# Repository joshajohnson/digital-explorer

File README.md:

Digital explorer board for common embedded protocols (UART, I2C, SPI, WS2812).

More info here: https://joshajohnson.com/digital-explorer-board/

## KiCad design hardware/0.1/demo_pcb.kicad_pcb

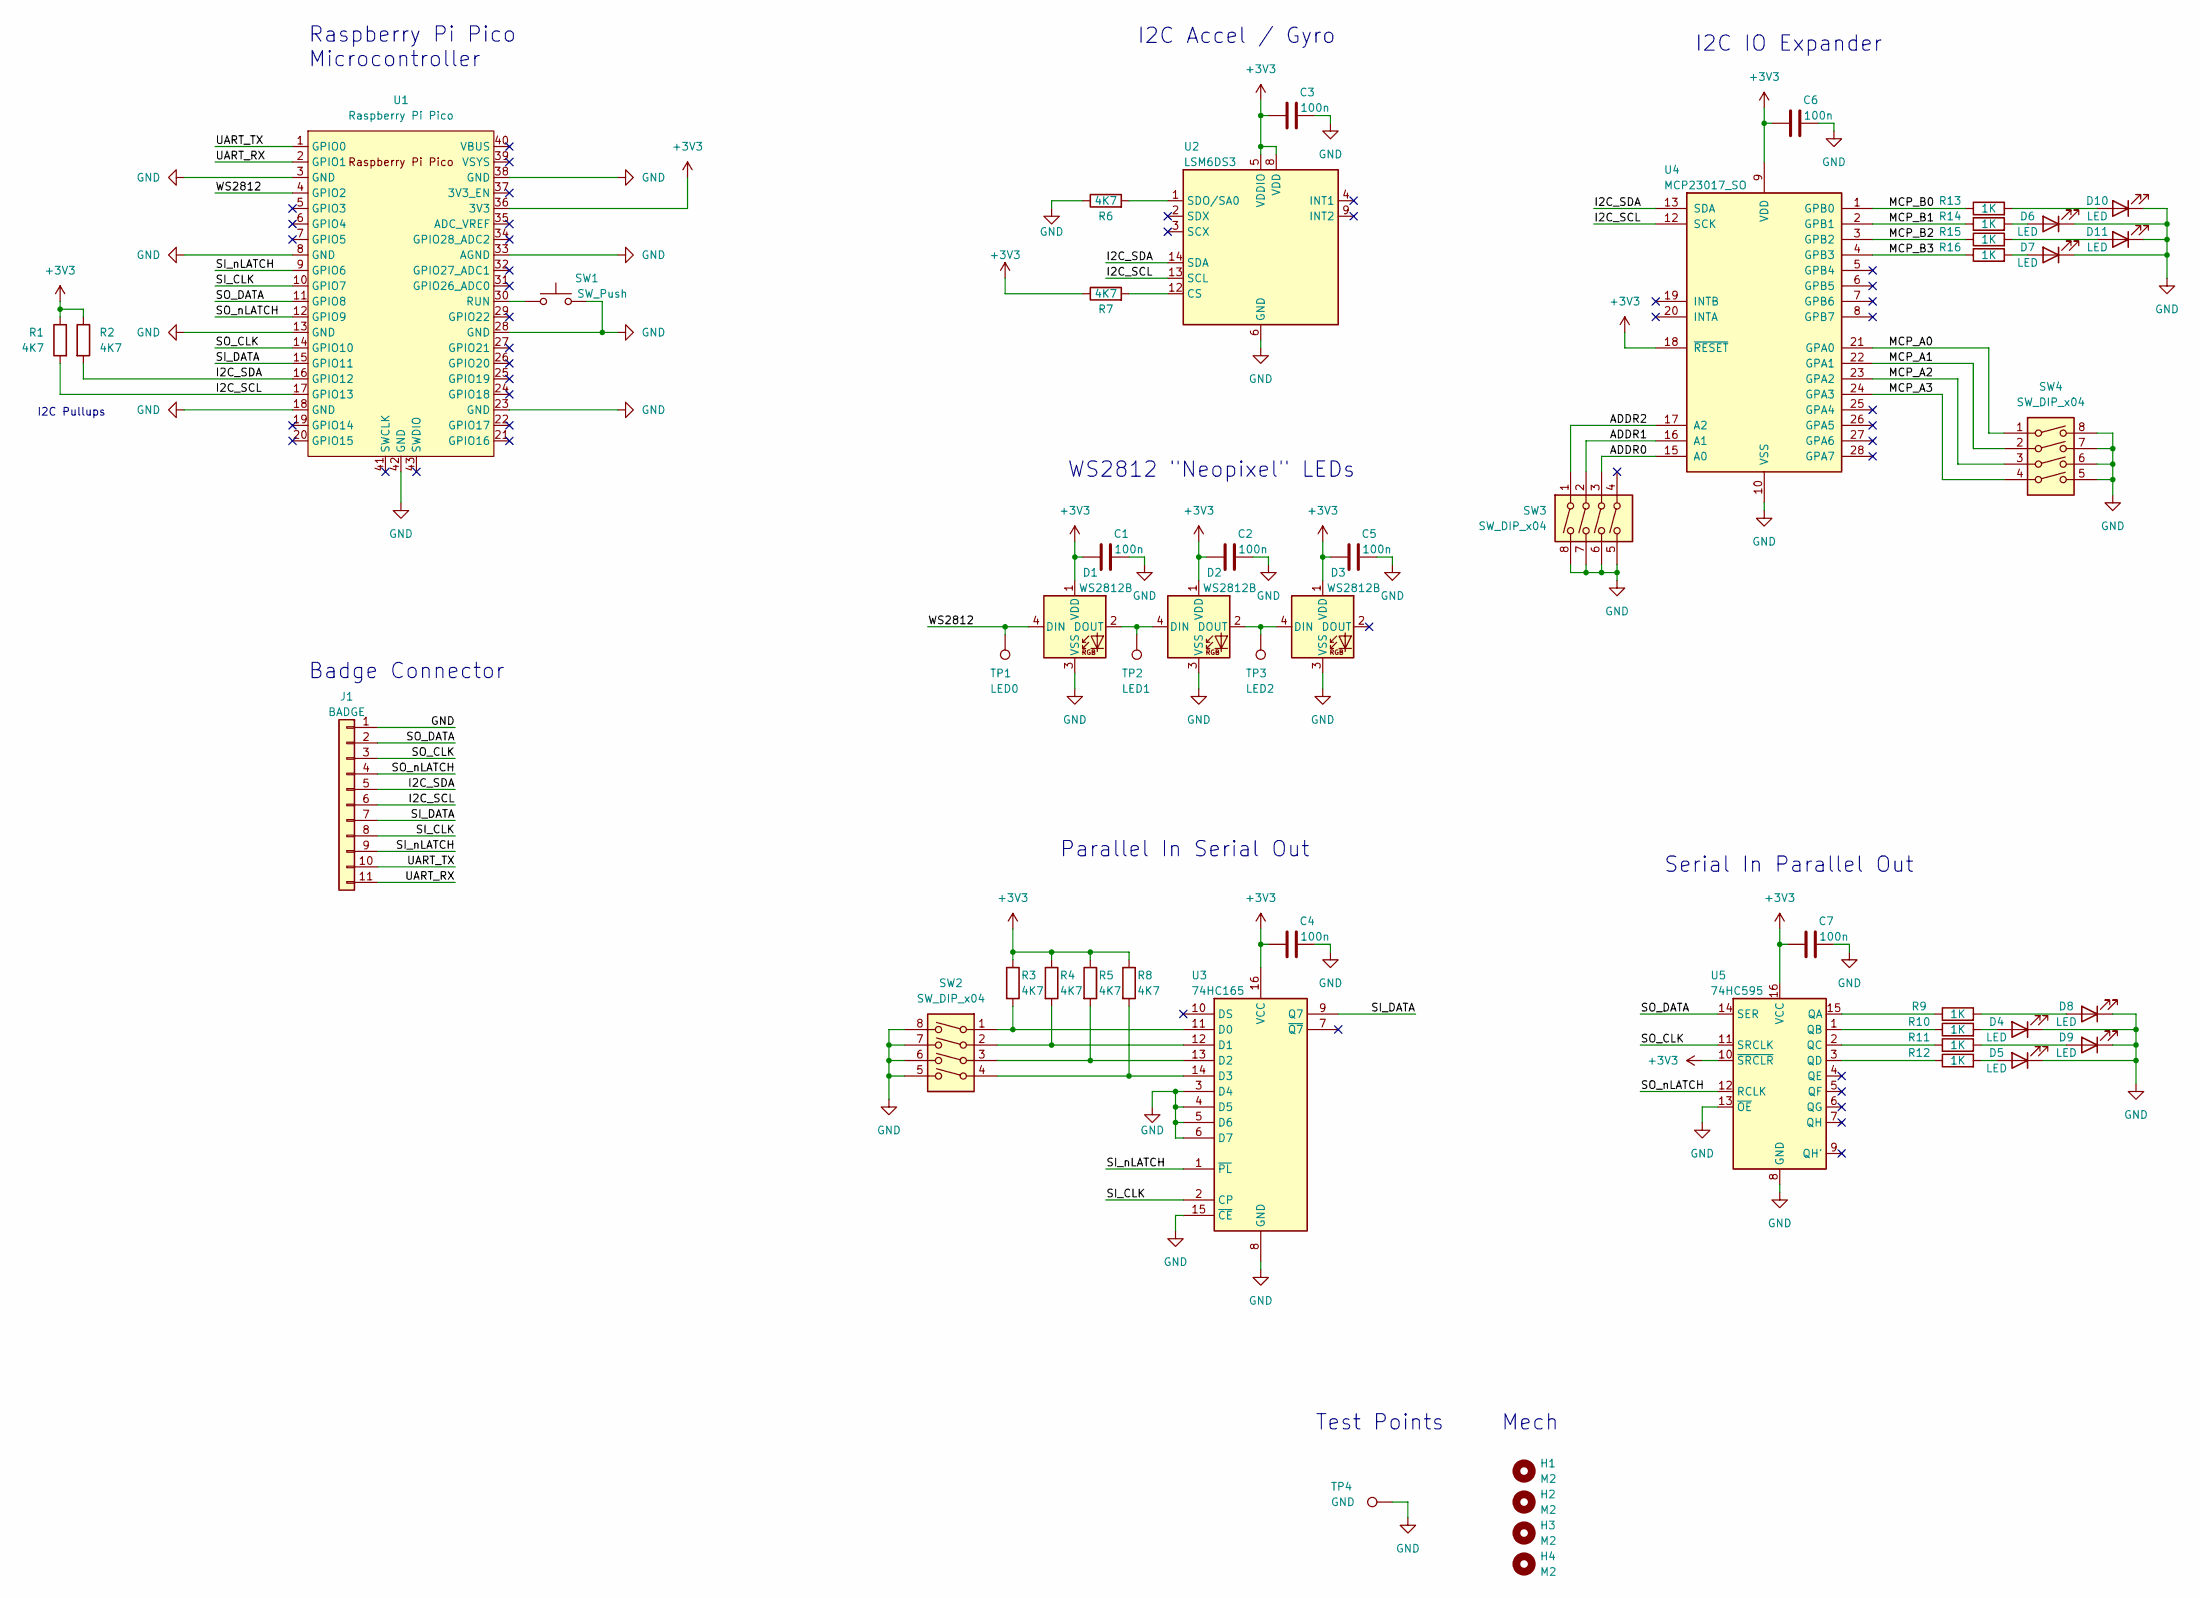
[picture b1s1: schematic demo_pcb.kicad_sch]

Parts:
C1, C2, C3, C4, C5, C6, C7: 100n; C_0603_1608Metric; LCSC C14663
D1, D2, D3: WS2812B; LED_WS2812B_PLCC4_5.0x5.0mm_P3.2mm
D4, D5, D6, D7, D8, D9, D10, D11: LED; LED_0603_1608Metric; LCSC C2286
H1, H2, H3, H4: M2; MountingHole_2.2mm_M2_DIN965_Pad
J1: BADGE; PinSocket_1x11_P2.54mm_Horizontal
R1, R2, R3, R4, R5, R6, R7, R8: 4K7; R_0603_1608Metric; LCSC C23162
R9, R10, R11, R12, R13, R14, R15, R16: 1K; R_0603_1608Metric; LCSC C21190
SW1: SW_Push; SW_SPST_PTS810
SW2, SW3, SW4: SW_DIP_x04; SW_DIP_SPSTx04_Slide_9.78x12.34mm_W7.62mm_P2.54mm; LCSC C99418
TP1: LED0; PinHeader_1x01_P2.54mm_Circle
TP2: LED1; PinHeader_1x01_P2.54mm_Circle
TP3: LED2; PinHeader_1x01_P2.54mm_Circle
TP4: GND; PinHeader_1x01_P2.54mm_Circle
U1: Raspberry Pi Pico; RPi_Pico_SMD_TH
U2: LSM6DS3; LGA-14_3x2.5mm_P0.5mm_LayoutBorder3x4y; LCSC C95230
U3: 74HC165; SO-16_3.9x9.9mm_P1.27mm; LCSC C5613
U4: MCP23017_SO; SOIC-28W_7.5x17.9mm_P1.27mm; LCSC C629440
U5: 74HC595; SO-16_3.9x9.9mm_P1.27mm; LCSC C5947

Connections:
+3V3: C1.1, C2.1, C3.1, C4.1, C5.1, C6.1, C7.1, D1.1 (VDD), D2.1 (VDD), D3.1 (VDD), R1.1, R2.1, R3.1, R4.1, R5.1, R7.1, R8.1, U1.36 (3V3), U2.5 (VDDIO), U2.8 (VDD), U3.16 (VCC), U4.9 (VDD), U4.18 (~RESET), U5.10 (~SRCLR), U5.16 (VCC)
/ADDR0: SW3.3, U4.15 (A0)
/ADDR1: SW3.2, U4.16 (A1)
/ADDR2: SW3.1, U4.17 (A2)
/I2C_SCL: J1.6, R1.2, U1.17 (GPIO13), U2.13 (SCL), U4.12 (SCK)
/I2C_SDA: J1.5, R2.2, U1.16 (GPIO12), U2.14 (SDA), U4.13 (SDA)
/MCP_A0: SW4.1, U4.21 (GPA0)
/MCP_A1: SW4.2, U4.22 (GPA1)
/MCP_A2: SW4.3, U4.23 (GPA2)
/MCP_A3: SW4.4, U4.24 (GPA3)
/MCP_B0: R13.1, U4.1 (GPB0)
/MCP_B1: R14.1, U4.2 (GPB1)
/MCP_B2: R15.1, U4.3 (GPB2)
/MCP_B3: R16.1, U4.4 (GPB3)
/SI_CLK: J1.8, U1.10 (GPIO7), U3.2 (CP)
/SI_DATA: J1.7, U1.15 (GPIO11), U3.9 (Q7)
/SI_nLATCH: J1.9, U1.9 (GPIO6), U3.1 (~PL)
/SO_CLK: J1.3, U1.14 (GPIO10), U5.11 (SRCLK)
/SO_DATA: J1.2, U1.11 (GPIO8), U5.14 (SER)
/SO_nLATCH: J1.4, U1.12 (GPIO9), U5.12 (RCLK)
/UART_RX: J1.11, U1.2 (GPIO1)
/UART_TX: J1.10, U1.1 (GPIO0)
/WS2812: D1.4 (DIN), TP1.1, U1.4 (GPIO2)
GND: C1.2, C2.2, C3.2, C4.2, C5.2, C6.2, C7.2, D1.3 (VSS), D2.3 (VSS), D3.3 (VSS), D4.1 (K), D5.1 (K), D6.1 (K), D7.1 (K), D8.1 (K), D9.1 (K), D10.1 (K), D11.1 (K), J1.1, R6.1, SW1.2, SW2.5, SW2.6, SW2.7, SW2.8, SW3.5, SW3.6, SW3.7, SW3.8, SW4.5, SW4.6, SW4.7, SW4.8, TP4.1, U1.3 (GND), U1.8 (GND), U1.13 (GND), U1.18 (GND), U1.23 (GND), U1.28 (GND), U1.33 (AGND), U1.38 (GND), U1.42 (GND), U2.6 (GND), U2.7 (GND), U3.3 (D4), U3.4 (D5), U3.5 (D6), U3.6 (D7), U3.8 (GND), U3.15 (~CE), U4.10 (VSS), U5.8 (GND), U5.13 (~OE)
unnamed: D1.2 (DOUT), D2.4 (DIN), TP2.1
unnamed: D2.2 (DOUT), D3.4 (DIN), TP3.1
unnamed: D4.2 (A), R10.2
unnamed: D5.2 (A), R12.2
unnamed: D6.2 (A), R14.2
unnamed: D7.2 (A), R16.2
unnamed: D8.2 (A), R9.2
unnamed: D9.2 (A), R11.2
unnamed: D10.2 (A), R13.2
unnamed: D11.2 (A), R15.2
unnamed: SW1.1, U1.30 (RUN)
unnamed: R7.2, U2.12 (CS)
unnamed: R6.2, U2.1 (SDO/SA0)
unnamed: R3.2, SW2.1, U3.11 (D0)
unnamed: R4.2, SW2.2, U3.12 (D1)
unnamed: R5.2, SW2.3, U3.13 (D2)
unnamed: R8.2, SW2.4, U3.14 (D3)
unnamed: R9.1, U5.15 (QA)
unnamed: R10.1, U5.1 (QB)
unnamed: R11.1, U5.2 (QC)
unnamed: R12.1, U5.3 (QD)

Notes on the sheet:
Badge Connector
I2C IO Expander
Parallel In Serial Out
Raspberry Pi Pico Microcontroller
I2C Pullups
WS2812 "Neopixel" LEDs
Test Points
Mech
I2C Accel / Gyro
Serial In Parallel Out

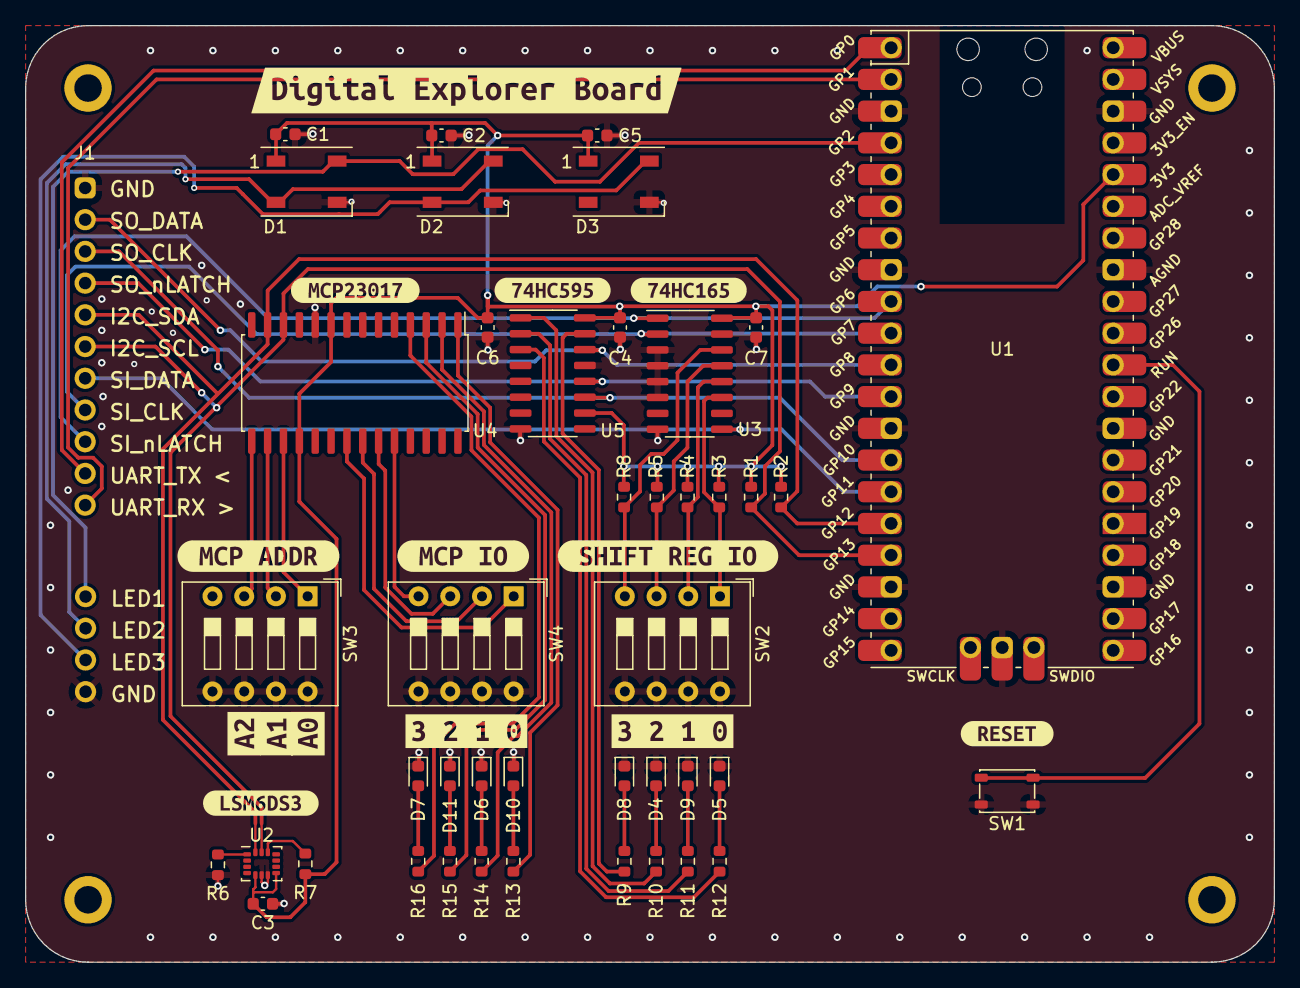
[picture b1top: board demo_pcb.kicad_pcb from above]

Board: 2 copper layers, 100.0 x 75.0 mm, 66 parts (0 on the bottom side), 45 nets.

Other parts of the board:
kibuzzard-64BE6A65: G***; kibuzzard-64BE6A65
kibuzzard-64BE6A90: G***; kibuzzard-64BE6A90
kibuzzard-64BE68F6: G***; kibuzzard-64BE68F6
kibuzzard-64BE673E, kibuzzard-64BE673E#2: G***; kibuzzard-64BE673E
kibuzzard-64BE676D: G***; kibuzzard-64BE676D
kibuzzard-64BE679E: G***; kibuzzard-64BE679E
kibuzzard-64BE6544: G***; kibuzzard-64BE6544
kibuzzard-64BE6560: G***; kibuzzard-64BE6560
kibuzzard-64BE6573: G***; kibuzzard-64BE6573
kibuzzard-64BE6790: G***; kibuzzard-64BE6790
kibuzzard-64BE6934: G***; kibuzzard-64BE6934
kibuzzard-64BE6949: G***; kibuzzard-64BE6949
kibuzzard-64BFA375: G***; kibuzzard-64BFA375

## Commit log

2023-09-21 add kicad files
2023-09-21 add rpi pico software
2023-09-23 add sch
2023-09-23 add \r\n to uart
